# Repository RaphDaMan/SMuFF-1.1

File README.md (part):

# Welcome to the SMuFF project

Here's the official firmware package for the **S**mart **Mu**lti **F**ilament **F**eeder, as published on [Printables](https://www.printables.com/de/model/194737-smuff-v6-smart-multi-filament-feeder-with-bondtech) and [Thingiverse](https://www.thingiverse.com/thing:3431438). Read the full story on how it came to life on my official [SMuFF homepage](https://sites.google.com/view/the-smuff/).

If you like this project and find it useful, you may consider [donating](https://sites.google.com/view/the-smuff/downloads/assembly-manual#h.m5ewgcp0jfk6).

To use this firmware, you have to [compile it](https://sites.google.com/view/the-smuff/how-to/tutorials/compile-the-firmware?authuser=0) and flash it to one of these (already supported) controller boards:

| Board |  |
|------------|-----|
| Bigtreetech [SKR mini E3 V3.0](https://www.biqu.equipment/products/bigtreetech-skr-mini-e3-v2-0-32-bit-control-board-for-ender-3) |**recommended** |
| Bigtreetech [SKR mini E3-DIP V1.1](https://www.biqu.equipment/products/bigtreetech-skr-e3-dip-v1-0-motherboard-for-ender-3)||
| Bigtreetech [SKR mini E3 V2.0](https://www.biqu.equipment/products/bigtreetech-skr-mini-e3-v2-0-32-bit-control-board-integrated-tmc2209-uart-for-ender-4) ||
| Bigtreetech [SKR mini V1.1](https://www.biqu.equipment/collections/control-board/products/bigtreetech-skr-mini-v1-1-motherboard-32-bit-arm-equipped-with-tmc2208-v2-1-tmc2130-spi-driver-stepstick-for-3d-printer-desktop?variant=20361870377058)||

The Bigtreetech SKR mini series boards are very small and yet powerful because of the 32-Bit STM Microcontroller Unit.

Of course, this firmware can also be configured to run on any other controller board, as long as it meets the specifications. Although you might be able to utilize older 8 bit boards, I don't recommended it - you'll most probably run out of memory (Flash/RAM) very soon. I recommend using a 32 bit controller board instead.
Make sure your board of choice has at least **256K** of Flash memory, **48K** of (S)RAM and all other components needed, which are at least:

+ two stepper motor drivers (sockets)
+ two endstop connectors
+ one servo connector (or two spare I/O pins for Software-I2C)
+ an onboard SD-Card
+ one spare serial port (USB or TTL)
+ a 128 x 64 pixel display connector
+ a rotary encoder connector

Simply create a new build environment in your **platformio.ini** and adopt the settings according to your controllers hardware in your custom **pins.h** file.

The configuration files **\*.json** and **debug.txt** have to be copied into the root folder of your SD-Card for the controller board. Hence, changing runtime parameters doesn't require recompiling the firmware. Just edit the settings from within the built-in menus or the [WebInterface](https://github.com/technik-gegg/SMuFF-WI), save them and reboot.

I've added the option to run GCode scripts for automated testing of your hardware.
In the **test** folder you'll find some sample scripts. Copy the folder over to your SD-Card and pick a script from within the menu to start the test run. Once started, the test will run infinitelly until you stop it.
Each test result will be displayed on the LCD and also sent to the log serial port (which is the USB port, if not defined otherwise).

For more information about building the SMuFF and some more detailed stuff, head over to my official [SMuFF homepage](https://sites.google.com/view/the-smuff/) or to my [Discord server](https://discord.com/invite/BzZ3rBf).

---

## Credit where credit is due

A special thanks to the folks who have shared the following libraries/knowledge, on which the SMuFF firmware builds upon:

+ [Adafruit](https://github.com/technik-gegg/Adafruit-PWM-Servo-Driver-Library.git) for the PWM Servo library
+ [Benoît Blanchon](https://github.com/bblanchon/ArduinoJson.git) for the Arduino JSON library
+ [Bill Greinman](https://github.com/greiman/SdFat) for the SD-Card library
+ [Oliver Kraus](https://github.com/olikraus/U8G2_Arduino.git) for the U8G2 display library
+ [teemuatlut](https://github.com/teemuatlut/TMCStepper) for the TMC-Stepper library
+ [the creators of the](https://github.com/technik-gegg/SoftWireSTM32/) SoftWireSTM32 library
+ [Tom Schimansky](https://github.com/TomSchimansky/CustomTkinter) for the Custom Tkinter Python package
+ [Akash Bora](https://github.com/Akascape) for the CTkMessagebox and CTkToolTip packages
+ [Scott Campbell](https://www.circuitbasics.com/arduino-thermistor-temperature-sensor-tutorial/) for sharing his knowledge about Thermistor handling

---

## Recent changes

**3.30** - Filament-Dryer integration

+ added fully functional Filament-Dryer (controller) by utilizing the Bed-Heater and Thermistor on the SKR E3 V3.0 board. Read all the details about this new feature [here](https://sites.google.com/view/the-smuff/how-to/build/the-filament-dryer). In order to use it, you have to compile the firmware with the *USE_DRYER* option and copy the new **dryer.mnu**, the updated **main{0-4}.mnu** files over to the *menus* folder and the **DRYER.json** file to the root folder of the SMuFFs SD-Card. Also copy the *help* folder to the SD-Card, since some GCodes were added/updated.
+ added GCode **M141** for controlling the new Filament-Dryer feature.
+ updated GCode **M106** in order to enable controlling fans 1 & 2 for the Filament-Dryer (will work only on SKR E3 V3.0).

**3.29** - Integrated Heater functions / SMuFF-Backbone

+ added code to control the (Bed-) heater on the SKR E3 V3.0.
+ added some code changes needed for the [SMuFF-Backbone board](https://sites.google.com/view/the-smuff/how-to/build/the-smuff-backbone).

**3.28** - minor changes

+ added option for 4th DC motor driver board (Waveshare/FeatherWing - for future use).
+ added option for up to two AHT-10 Temperature/Humidity sensor boards (for future use).
+ added GCode **M105** for reading out Temp./Humidity sensors.
+ refactored some of the code, i.e. moved code from SMuFF.cpp to own modules.

**3.27** - minor bug fixes

+ fixed bug on **FeatherWing DC-Motor Board** causing not all motors were able to spin because of the wrong pin assignment.
+ corrected help files for **M3/M4** GCodes (parameter **S** denotes the **Tool** but not neccessarily the **Motor** number).
+ fixed bug on **SKR E3-DIP V1.1** not beinig able to set relay pin to **Y-STOP** due to conditional compiling constraints.
+ corrected some flaws in *testrun()* not correctly reporting "feeding errors" as they occur.

**3.26** - minor change

+ moved scanning for I2C devices after display has been initialized, so it becomes obvious when the I2C scan is hanging, which happens if no I2C devices are attached to the bus.

**3.25** - minor fixes/changes

+ restricted scanning of the I2C bus to valid slave addresses (0-7 and 120-127 are reserved addresses). Although this didn't cause any error yet, it could have caused some unwanted effects in the future.
+ added a new option to route debug messages to other than the default Serial 2 (a.k.a. TFT-Header): Create a file in the root folder of the SD-Card named:
  + **dbg2usb.txt** for Serial 0 (a.k.a. USB)
  + **dbg2exp.txt** for Serial 1
  + **dbg2oth.txt** for Serial 3

   **Keep in mind:** These files need no content. Not every port (except USB) is available on every board, it depends on board and configuration. To reset sending debug messages to default Serial 2, delete or rename the file.
+ added the **Adafruit Stepper + DC Motor FeatherWing** board as a 2nd option for the Spool-Rewinder controller. To use it, you have to define **USE_SPOOLMOTOR_FEATHERWING** in addition to **USE_SPOOLMOTOR** in the *config_defaults* and/or tick the according option in the *Firmware Build Configurator*.

**3.24** - added new "Firmware-Build Configurator"

+ made the build configuration easier by adding a custom dialog (Python/Ctk). Now, the *PROJECT TASKS* treeview only contains the basic build environments for each supported controller. Everything else can now be configured right after clicking on the **Build** task using this dialog:

This is by far more convenient than parsing through the *platformio.ini* or trying to find the build environment you want.
Tooltips will show up when hovering over the checkboxes, which briefly explain why you would use this option.
After the build you'll find a **readme-build.txt** file in the output folder, listing the options that have been set for this particular build.
To define a set of **personalized default settings** depending on the controller used, one can list them under the *config_defaults* section in *platformio.ini*.
*Please be aware that for using this feature, PlatformIO needs to install some Python packages once. This happens automatically at your very first build.*
+ updated SdFat library reference to 2.2.0
+ added the option to use the "old" clock settings (those recommended by STM) for the SKR E3 V3.0 board instead of the new ones introduced in version 3.23.
+ added a couple more debug messages while the firmware is being initialized.

**3.23** - bugfix, Motorized Spool Rewinder option added

+ fixed the bug that caused some (newer) SKR E3 V3.0 boards not being recognized (enumerated) when connected via USB.
+ added **_SPM** build environments, which allow utilizing the [Motorized Spool Rewinder](https://sites.google.com/view/the-smuff/how-to/build/the-spool-rewinder). To use this option, you have to copy the *help* and *menus* folders to your SMuFFs SD-Card. Also, please notice the added content in **MATERIALS.json**.
+ added GCodes **M3**, **M4** and **M5** to allow controlling the spool motors of the *Motorized Spool Rewinder*.

**3.22** - reorganized Build Environments

+ reorganized Build Environments as announced in 3.21.
.
+ added include of <stdint.h> to SMuFF.h, since latest builds seem to fail.

**3.21** - some changes based on the previous release

+ reworked the Build Environments in **platformio.ini**
 Since the **SKR E3 V3.0** has become the most dominant contoller board and the others are getting more and more outdated, I've decided to get rid of some of the Build Environments for "older boards" and add all the possible permutations for the E3 V3.0 instead. The suffixes are meant to be self-explanatory but as a hint: **NPX** means NeoPixels (on tools), **MS** means Multiservo and **DDE** means Direct Drive Extruder.
 Here's what the *PROJECT TASKS* treeview in VSCode now looks like:
 
 Simply open the Build Enviroment that matches your setup and click on "Build".
 Outdated Build Environments are still contained in the ini-file but need to be un-commented in order to make them show up in the *PROJECT TASKS* treeview.
+ the (FYSECT / BTT / MKS) **MiniPanel 12864 V2.1** display has become the default option now. It's the cheapest and easiest to source display, so I declared it the "standard".
+ while playing around with the new behaviour of **USE_NUM_PIXELS** introduced in the previous release, I figured, it's far easier to have the number of LEDs configurable at runtime and thus, I've moved it to the SMuFF configuration file. Hence, this definition is now gone from the platformio.ini!
When you update to this version, please keep in mind to also copy the new **display.mnu** and **m205.txt** to your SMuFF's SD-Card, into the folders *menu* and *help* accordingly.
+ I also found an unpleasant but logical behavior in the *Marquee* animation when more than 7 LEDs are in use: It skips LEDs because on the beatsin() calculation and BPM settings, so I fixed that.
+ while I was at it, I also added two new Idle-Animations: Rainbow and Cylone. Thus, you need to copy the **anim-type.opt** to the *options* folder as well. Then pick the one that you fancy the most from the *Display menu*.

**3.20** - small feature change

+ corrected the behaviour of the **USE_NUM_PIXELS** definition in *platformio.ini*. This defines how many **NeoPixel LEDs** one plans to use for one tool (which usually is: "1 LED per tool").
This feature comes in handy when you're using a NeoPixel strip with a higher density. The "standard" NeoPixel strips come with a density of 60 LEDs/meter but they're also available in 30, 72, 96, 144, 240 or even 332 LEDs/m.
It turned out, that on strips with **144 LEDs/m** the LED spacing is around 7mm (i.e. 1000/144 = 6.94), which corresponds to 3 LEDs for 21mm! Coincidentally, this is also the exact width of one Filament-Guide. Hence, using a 144 LED/m strip saves you from the tedious job of cutting a strip and re-soldering the LEDs in order to get them into the right position. Simply use a longer strip (3 LEDs * number_of_tools) and set **USE_NUM_PIXELS** to 3 before compiling the firmware.

**3.19** - bug fix

+ fixed bug in Selector homing. When homed, SMuFF wasn't able to select tools because the Selector endstop was still triggering.

**3.18** - minor bug fix

+ fixed bug in displaying menu items

**3.17** - minor bug fixes / optimizations

+ fixed bug in platformio.ini for SKR Mini environment.
+ fixed bug in *NeoPixels on Tools*, if more than 5 tools are being used. Init of the NeoPixels happened before the Config was read and hence the count of tools/NeoPixels was incorrect.
+ optimized code for the steppers (*ZStepperLib*) yet again. The *isrStepperTimerHandler()* method now has an overall runtime of about **15uS** on a **STM32F1** MCU running at 72MHz.
+ changed some methods in timers.h/timers.cpp in order to shave off some microseconds in processing time.
+ fixed bug in synchronous movement of the steppers. Feeder stepper wasn't moving at the same pace as the DDE Feeder.
+ changed the USB signature to **STMicroelectronics SMuFF 3.x**. This way it's easier to distinguish which controller is for the SMuFF on the Raspberry Pi.
+ added meaningfull description headers to all methods in *ZStepperLib*, so it can be reused in other projects.
+ moved hardware Debug-Pin for E3-DIP controller from **Y-STOP** to **SWCLK** for a cleaner wave form. Since this is for my debugging only, you don't have to care much about this change.
+ removed TMC library and build flags from **E3-DIP** and **SKR MINI**, since those boards have no native TMC support (i.e. not being controlled through serial or SPI) and hence TMC drivers are running in "Standalone" a.k.a. "A4988" mode.
+ modified the **Acceleration Distance** behaviour. If this value is set to **0**, SMuFF will use 20% of the total distance for accel/decel, which results in a somewhat smoother acceleration/deceleration.
+ fixed bug stepper movement not stopping on endstop trigger. For some (still undiscovered) reason, the endstop ISR doesn't fire while steppers are moving.
+ changed/removed a couple of debug messages to make them a bit more meaningful.

**3.16** - bug fixes / enhancements / cleanup

+ **changed the stepper motors timer prescaler from 24Mhz to 2MHz** (internally 4MHz). This means, you **must** adjust your stepper ticks, otherwise steppers are going to turn terribly slow! Had to do this in order to gain more granular control over the stepper motors at lower speeds.
*Rule of thumb: Divide your current speed settings (Max. speed, Accel. speed, Purge speed, etc.) roughly by 10.*
The stepper timer in fact is running on double the frequency (4MHz) in order to achieve a longer pulse on the stepper driver, because now every 1st tick is used to set the STEP signal, every 2nd to reset the STEP signal. This makes the *Step-Delay* setting unnecessary and you should set it to 0. Though I left this setting in the config, just in case one needs it.
+ changed behaviour of "Unload retraction". If a value is set, it will only be executed if filament is fully loaded (down to nozzle). Keep in mind that this feature is used to shorten the filament remains when using the Cutter and yet only works on a Bowden setup.
+ changed data-type in *purgeFilament()* from uint16_t to double for more accurate purging.
+ changed the method of debug outputs in endstop interrupt functions, since sending data to serial ports from within ISR routines is always a bit critical and may block or crash the controller.
+ added **DEV4** debug flag for a more granular output control of debug messages (i.e. printing incoming GCodes, memory stats, ...).
+ updated GCode **M100** to determine free system memory (RAM). Before, this GCode only returned "ok".
+ added printing out memory stats every minute if *DEV4* debug flag is set.
+ removed the "*Mirroring the display on a VT-100 terminal*" feature introduced in V2.24 completely. Although it was nice to have back then, the software options around the SMuFF have evolved. Hence this feature is obsolete now and was only messing up the source code.
+ removed the (meanwhile) obsolete conditional code for FastLED library. My modified Adafruit NeoPixel library is covering all that's needed.
+ overhauled the code for handling the NeoPixels on tools. NeoPixels will not update as long as one of the stepper motors is spinning (Feeder / Selector), which makes the steppers run smoother.
+ added parameter **P** to GCode **M700** (load filament) in order to purge material (after it's being loaded). If no *value* (e.g. *M700 P*) is given, it'll purge the configured purge amount, otherwise the length of filament given in *value* (e.g. *M700 P12.34*).

  **[ Bug fixes ]**

+ fixed the bug that puts a "loading" dialog on the display while in *Testrun mode* (kudos to **palkovnik807**).
+ fixed the bug where retries were not being decremented while unloading filament (a.k.a "infinite loop" if unloading went wrong).
+ fixed a potential buffer overflow in *drawPurgingMessage()* and *printPeriodicalState()* functions.
+ fixed a bug that may have caused the MS1/MS2/MS3 pins being set up wrong on the **E3-DIP V1.1** (only), because the according pins on the MCU were in an undefined state. Now those pins are being set to LOW (0V) at startup.

**3.15** - minor changes / bug fixes

+ added option **NEVER_DISABLE_SERVOS** in *platformio.ini* section *'other'* which will inhibit disabling servos after they had been moved. The default behaviour is that the SMuFF will disable the PWM signal on **Wiper** and **Cutter** servos after wiping/cutting, because some servos run less jittery when disabled.
However, it turned out that disabling the PWM signal on some servos causes those servos eventually start moving out of the blue. Allowing the PWM signal to stay active helped fixing this issue.
If you discover random movements on your Wiper/Cutter servo, activate this new option before compiling the firmware.
*This option however doesn't influence the behaviour on the Multiservo board(s) - which still are the better option for driving servos.*
+ fixed the bug that sometimes caused the filament not being fully retracted (i.e. Feeder endstop not triggered). Happens only if the configured "Bowden length" value doesn't match the real distance or the filament "slipped" during retraction. In such case the Feeder was supposed to retry until the endstop has triggered but didn't due to wrong condition checking. Thanks to **palkovnik807** on Discord for pointing it out.
+ fixed the bug that caused the **DDE Feeder** not doing a purge under certain conditions because the stepper wasn't enabled. Thanks to **Thyom** on Discord for finding it.
+ added printout of DDE Feeder endstop state for GCode **M119**, in case SMuFF is configured for DDE.

**3.14** - minor changes / bug fix

+ added option **USE_NUM_PIXELS** in *platformio.ini*. Usually, the number of Neopixels matches the number of tools but in some special case you may have more Neopixels on your strip then tools. In order to make the animations using all pixels, enable this definition and set its value to the according number.
+ fixed bug where Lid servo didn't close before unloading when Cutter has been configured as sitting "on top".

**3.13** - Changes for Duet3D and Serial display / some bugfixes

+ fixed bug in TMC driver **Stealth-Mode setting** via SMuFF-WI. Value was accidentally inverted.
+ fixed bug that caused a compilation failure when using the *SKR_E3_30_RET6___DDE* build environment.
+ added [SMuFF-Backbone](https://sites.google.com/view/the-smuff/work-in-progress?authuser=0#h.m19pbkoy3v6p) schematic and PCB design.
+ added **DuetSerial** (port) setting to **SMUFF.json** and menus. You **must** now define the serial port where the Duet3D/RRF is connected to (set to Ser.1 by default). This serial port will only be taken into account if the SMuFF is configured for Duet3D/RRF. For this option you need to copy the modified **options.mnu** and **duet3d.opt** files into the according folders on your SMuFFs SD-Card.
+ added **DspSerial** (port) setting to **SMUFF.json**. The Display serial port can only be configured either through the **-D DISPLAY_SERIAL_PORT** definition in *platformio.ini* or manually in SMUFF.json but not from the menus (because there will be no menus in this mode). See notes on **USE_SERIAL_DISPLAY** for version **3.00** down below.
+ updated **M42** & **M280** & **M205** help files (for Multiservo use).
+ added Dialogs and Sound support on SMuFF-WI when *USE_DISPLAY_SERIAL* is enabled.
+ added **SWAP_SELECTOR_ENDSTOP** build option for those who experience the X-STOP (used for Selector) is not being triggered on a **SKR E3 V3.0**. With this option enabled, the firmware expects the Selector endstop to be connected to *Y-STOP* rather than *X-STOP*.
+ added *JAM* flag in periodical status messages; This is being used in my OctoPrint/Klipper plugins to indicate whether or not the tool change has failed for some reason.
+ added option to switch the *Debugger Serial Port* from within **debug.txt** on startup, without the need for recompiling the firmware. To use this option simply add a **;x** after the value, whereas *x* determines a port number between **0** and **3**. Port **0** always indicates the **USB** serial port, whereas ports **1..3** depend on the controller board you're using (*port 2 is the default value and is assigned to the **TFT** header on most boards*).
*Keep in mind:* This setting will vanish once you set the debug flags via GCode **M111** and store them using **M500**.
+ added option to switch the *Debugger Serial Port* on the fly via **M205** GCode. To use it, simply apply parameters **P"ChangeDbg" Sx**, whereas *x* is the number of the new serial port in the range of **0..3** (see description above).
*Keep in mind:* This setting is temporary and will be reset at the next boot.
+ added option to filter in help files. After the **?** append the phrase to filter for. For example: **M205?dist** will only show the header and all lines containing the string *"dist"*.

**3.12** - Changes for the MULTISERVO option

+ reworked **MULTISERVO** option. For one it's now named *USE_MULTISERVO* for more consistency throughout the other options. For the other, it's now being used to configure all servos to control them via an external board (Adafruit Multiservo/FeatherWing/ [SMuFF-Backbone](https://sites.google.com/view/the-smuff/work-in-progress?authuser=0#h.m19pbkoy3v6p) board). This external board is always being controlled by using software I2C. The pins used for SW-I2C vary throughout the different controller boards.
+ the **USE_MULTISERVO** flag will become more importance in the future, hence I moved that option to the *[other]* section of *platformio.ini*.
+ modified the external **SoftWireSTM32 library** which had a bug that caused that the library wasn't able to scan for devices on the I2C bus properly.
+ moved relay control pin on **SKR mini E3-DIP V1.1** from **MS3** pin of the Z-Axis driver socket (in DDE mode) to the **TH0** pin if the **USE_MULTISERVO** flag is set. This is because this signal is being used as the data pin (SDA) for the software I2C controlling the Adafruit Multiservo board.
+ added **USE_MULTISERVO_RELAY** flag to the compile options in order to control the relay via output #5 on the Multiservo board instead of *MS3*, *TH0* or *PROBE* pins. This will be the future method of controlling the relay switch. **Please notice:** This method requires a pull-up resistor of 4.7K - 10K, either on +5V or +3.3V to make the signal switch as intended. The reason being is that the outputs on the Multiservo board are configured as open-drain.
+ corrected build environment for **SKR mini V1.1** (FastLED library was still referenced instead of the Adafruit Neopixel library).
+ fixed the bug that caused the **SKR mini V1.1** to hang at startup (wrong *debugSerial* port has been initialized).
+ added a couple more meaningful error messages to the GCode interpreter.
+ changed **SERVOMAP.json** config file to reflect the new MUTISERVO options. Please copy this file over to your SMuFF's SD-Card.
+ changed **ServoMinPwm** and **ServoMaxPwm** settings in SMUFF.json. These settings work better with the Multiservo boards. Copy the modified file over to your SMuFF's SD-Card and don't forget to reconfigure your servo angle settings.
+ added the two user controlled servo ports (USER1/USER2) to **M280** GCode and **M42** GCode when using the MULTISERVO option. Send M280 P1000 / P1001 if those ports are supposed to drive custom servos, or M42 P1000 / P1001 if those ports are configured to be used as output pins (i.e. to be switched on/off).
+ added **M260** GCode to allow scanning for I2C devices at runtime using the GCode interface.
+ updated some of the KiCad files to KiCad version 6.x

**3.11** - Some minor changes

+ added flashing of the "Periodical State sending" glyph on the display when it's enabled. Flashing happens at half the frequency of states being sent.
+ added current relay state (**E** / **I**) to "Periodical States".
+ changed output of **M122W** and **M503W**. *M122W9* and *M503W0* are now sending all state/configuration data at once, which makes SMuFF-WI connect faster.

**3.10** - Some minor changes / bug fixes

+ **removed SKR E3 V1.2** from the list of supported devices because this board isn't optimal for the SMuFF V6. Consider moving to E3 V2.0 or better E3 V3.0.
+ changed some default settings in *SMUFF.json* which fits better for V6 default configuration.
+ switched from FastLED to AdafruitNeoPixel library throughout for all boards.
+ fixed bug where DDE extruder wasn't reading out the endstop while retracting.
+ fixed bug with NeoPixel refresh.
+ added dedicated timer for NeoPixel refresh because the existing solution interfered with servos and steppers.
+ (re-) added timer for servos because the existing solution interfered with the stepper timer.
+ changed timer priorities and intervals to get rid of servo jitter.
+ changed priority on timers, so the stepper timer (and thus the stepper movement) is a bit more agile now.
+ added GCode command **M155** for fast switching of *sending periodical status messages*.
+ GCode **M205 help file** updated.
+ cleaned up *platformio.ini* by extending environments in *__DDE.
+ added GCode command **M562** to reset a *Feeder Jam* remotly.
+ added more status/error responses in order to make the Klipper module run smooth
+ added feeder states (SPL in periodical states) for all variants. This value is now (lower nibble: Splitter, upper nibble: non-Splitter):
  + 0x00 means *not loaded*
  + 0x01 means *loaded to Splitter*
  + 0x02 means *loaded to Nozzle*
  + 0x10 means *loaded to Selector*
  + 0x20 means *loaded to Nozzle*
  + 0x40 means *loaded to DDE*
+ added "JAMMED" state on display when feeder is being jammed

**3.00** - Moving from Maple to Arduino Core STM32 framework  

+ ported firmware from **Maple** to new **Arduino Core STM32** (stm32duino) framework in order to make boards with different MCUs available. This version is still compatible with the predecessor SKR controller boards, such as the SKR Mini/E3-DIP/V2.0.
+ added **debug.txt** to define the amount of debug messages being spit out without re-compiling the firmware. Also added the option of changing the debug level through GCode, which is **M111**. See *M111?* for details.
+ compiling the firmware without the **-D DEBUG** option will now reduce the memory footprint drastically. Although, removing debug messages completely will make your first setup much harder, so handle with care.
+ updated help files in *help* folder.
+ reduced the number of build environments in *platformio.ini*. Please note that **USE_DUET3D** has become obsolete and is now a runtime option. However, the **USE_DDE** flag still is the same and hence it's got its own build environment (*\*___DDE*).
+ added build options summary when compiling. This makes checking the build options you've set a breeze:

+ removed Servo-Timer. Servos are now served through the *General Purpose Timer*, which makes the servo timing more percise and thus the servos less jittery.
+ added flag **MIMIC_LIBMAPLE_USB_ID** in order to keep the USB ID compatible for use with my [OctoPrint plugin](https://github.com/technik-gegg/OctoPrint-Smuff). This setting is default for the "old" SKR E3 controller boards but not for newer boards.
+ added flag **SWAP_SERVOS** which will assign the Lid and the Cutter servos to the BL-Touch header for SKR E3 V1.2 / V2.0 / V3.0 (it swaps Wiper and Cutter servo signal pins).
+ added new build environment for **SKR E3 V3.0** controller board. This board has been fully tested and is ready to use.
+ added new build environment for **SKR E3 RRF** controller board. **Not tested yet!**
+ added **SyncSteppers** flag in SMUFF.json, which, if turned on, synchronizes movement of two or more steppers, so that they start and finish at the same time. Set by default.
+ eliminated code for *ZPortExpander* completely.
+ restructured **Options** menu on the display. Copy the new *options.mnu* file to the SMuFFs SD-Card (folder menus).
+ added **USE_SERIAL_DISPLAY** option for future use. ***Please be aware:** By setting this flag, no display code will be compiled into the firmware and hence the only way to control it is by using the WebInterface.*
+ added **USE_FAST_SW_SPI** build option for Creality  displays (or compatibles such as the BTT TFT). This allows you to simply connect the display through EXP1/EXP3 with the applied 10 pin cable, and still get a decent speed and responsiveness on the display.
+ added a couple of new STL files for Inlet-Guides and new SKR housing. Inlet-Guides are now available for 5 and 7 materials (thanks to maker **Defenc**). For a different amount of materials on the Inlet-Guides, please download the according [STEP file from Thangs](https://thangs.com/mythangs/file/55305).
+ fixed bug which caused the SMuFF to hang after showing the main menu.
+ refactored some code from **SMuFFtools.cpp** into *DisplayTools.cpp*, *SoundTools.cpp* *ServoTools.cpp* and *TerminalTools.cpp* for better maintainability.

---

**2.44** - Addition for alternative RRF boards

+ added inverting option for the *Busy* signal that goes to a endstop of a RepRap Firmware board (other than the Duet3D). This was needed since some of the alternatives might not be able to trigger upon the original signal. To use this option, you'll also need to copy the updated **options.mnu** file to the *menus* folder of your SMuFFs SD-Card.
Basic instructions for setting up a RRF (Duet3D) board can be found [here](https://sites.google.com/view/the-smuff/how-to/tutorials/configure-the-duet3d?authuser=0).
+ removed old code that might have disturbed Duet3D signals.
+ fixed a typo in the folder name which caused the E3 V1.2 version not being able to build correctly.
+ reorganized *Build Environments* in platformio.ini. This change allows you to pick some of the build options quickly. In the *Project Tasks* you'll now find different environments named after the controller board (i.e. **SKR_E3_12** for the SKR E3 Version 1.2) and three with the same name plus an extension named either **DDE**, **DUET** or **DDE+DUET**. The one without an extension is the "basic" version (no DDE, no Duet3D). **DDE** builds the firmware for the DDE option, **DUET** for the Duet3D (a.k.a. RRF) and **DDE+DUET** for a combination of both of the previously mentioned options. Thus, you don't have to mess with these settings in the [options] / [extruder] section anymore (the latter section has become obsolete now).
Keep in mind that you still have to set the correct **display** option before you build the firmware, in case you're using something else than the DIY display.
+ added **M118** GCode to enable you to send text (GCode) from the SMuFF/WI console to a specific serial port. Parameters are the same as for Duet3D/RRF fimrware, whereas **P**x defines the serial port, and **S**"..." defines the message to send. Please update you *help* folder with the latest files.

**2.43** - added new STLs

+ added new STL files for the small servo carrier. Please read [the instructions posted here](https://sites.google.com/view/the-smuff/work-in-progress?authuser=0#h.ssx9ayceh6f4).
+ updated version number to make the version check in WebInterface happy again.

**2.42** - some minor bug fixes/changes

+ made contrast setting a live function (contrast of the display will change as you rotate the knob, which makes it easier to set up).
+ corrected contrast setting after reading configuration on startup.
+ changed backlight color order on *FYSETC Minipanel* from GRB to RGB.
+ added SKR E3 RRF board to the collection. **This is experimental only and will not compile due to the lack of support for STM32F4 in some libraries. Do not use!**

**2.41** - some fine tuning on recent changes

+ added **DebugFreq** setting to **SMUFF.json** which allows to set the frequency (in Hz) applied to the hardware debug pin for testing purposes. This value can be changed during runtime via M205 GCode as well.
+ defined Duet3D signal pins (*DUET_SIG_FED_PIN* and *DUET_SIG_SEL_PIN*) to be on thermistor pins (THB and TH0). Because of the R/C filter on those pins signals are limited to a max. switching frequency of **100Hz**, which is sufficient for this purpose.
+ removed redundancy in display includes throughout all the Pins.h files. These are now located once in *Display/Display.h*.
+ corrected some pin defintions in all Pins.h files.
+ revived the SKR Mini V1.1 board (because it's still available and in use).

**2.40** - code reorganization and bug fixing

+ removed old boards, such as ESP32, SKR Mini, FYSETC AIO II, mainly because they're discontinued and just mess up the project.
*Because of this change the version number is now 2.4*
+ removed code for ESP32 entirely. As long as the ESP32 has such a deficit on I/O pins, it's not feasible as a SMuFF controller.
+ split up **Pins.h** to disentangle the confusing code for display pin definitions. Now each display type has it's own *DSP_xxx.h* header file and the initialization takes place in the according *Display/xxx.h* file instead of *SMuFF.cpp* and *SMuFF.h*.
+ reorganized code in order to reduce memory footprint and allow compiling for NeoPixels unconditionally. Due to usage of the PortExpander (PCF857X), which only purpose was to extend the amount of I/O ports on the ESP32, the memory footprint exploded. It's corrected now and the memory (RAM) footprint is slightly around 35% instead of 86%!
+ corrected pinout for standard RepRap display and FYSETC 12864 Minipanel on E3 V2.0 board.
+ improved drawing speed on the DIY OLED display for E3 V2.0 board.

**2.34 - 2.39** - skipped versions

**2.33** - bug fixing for DDE option

+ fixed a bug that caused stalling on the DDE stepper motor while purging because of wrong settings.
+ added more frequent status information for the WebInterface while swapping tools.

**2.32** - added Cutter position for DDE option

+ **moved main repository on Github to SMuFF-2.0 branch. No need to download from the SMuFF-2.0-(Experimental) anymore.**
+ added **CutterTop** option in SMUFF.json which was needed for the latest Orbiter-Extruder mod. For the Orbiter-Extruder you need to set this option to *false* because the Cutter sits below the DDE.

**2.31** - added Cutter handling for DDE option

+ added purging of filament when DDE is being used in conjunction with the Cutter in order to release the 2nd endstop. To use this, set the **PurgeDDE** flag in SMUFF.json accordingly.
+ fixed bug in feedToEndstop which caused an abort if the *InsLen* parameter was set too low.
+ added all **STL files** for V6 to this repository
+ added **Device** parameter in SMUFF.json. This string can be 15 charaters long and sets a distinct name for the current SMuFF device (i.e. the printer it is attached to). The name of the device will be show up in the WebInterface and also in GCode **M503**. This name can only be set/changed through the WebInterface or directly in the config file but not in the menu.

**2.30** - DDE option added

+ added **USE_DDE** flag in platformio.ini. Set this flag if you intend using the SMuFF on a Direct Drive Extruder. Further instructions you'll find on the [SMuFFs website](https://sites.google.com/view/the-smuff/how-to/tutorials/set-up-a-dde).
+ added new menu items in **options** menu for DDE. *Please notice:* The Use DDE flag can't be switched during runtime, it's only shown to indicate whether ot not this firmware was compiled for DDE.

**2.29** - Some critical changes, Splitter option added

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
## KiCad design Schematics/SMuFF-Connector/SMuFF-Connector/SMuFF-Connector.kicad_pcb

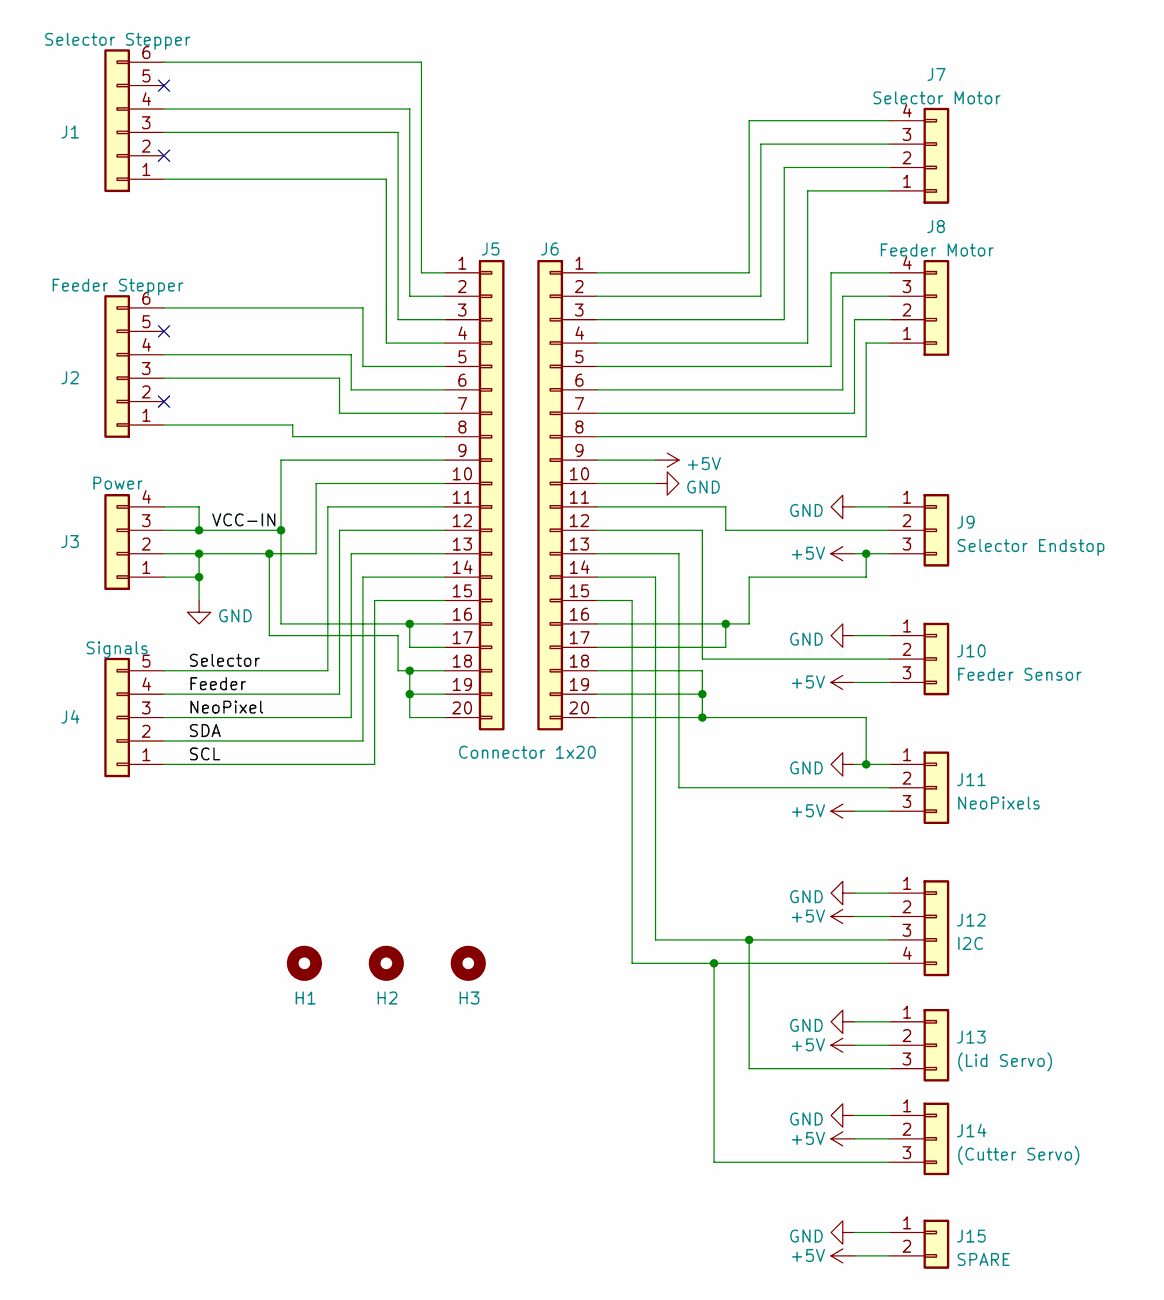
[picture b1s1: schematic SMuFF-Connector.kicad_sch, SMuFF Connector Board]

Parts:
H1, H2, H3: MountingHole; MountingHole_3mm
J1: Selector Stepper; JST_PH_B6B-PH-K_1x06_P2.00mm_Vertical
J2: Feeder Stepper; JST_PH_B6B-PH-K_1x06_P2.00mm_Vertical
J3: Power; JST_XH_B4B-XH-A_1x04_P2.50mm_Vertical
J4: Signals; JST_XH_B5B-XH-A_1x05_P2.50mm_Vertical
J5: Connector 1x20; PinHeader_1x20_P1.27mm_Vertical
J6: Conn_01x16; PinHeader_1x20_P1.27mm_Vertical
J7: Selector Motor; JST_XH_B4B-XH-A_1x04_P2.50mm_Vertical
J8: Feeder Motor; JST_XH_B4B-XH-A_1x04_P2.50mm_Vertical
J9: Selector Endstop; JST_XH_B3B-XH-A_1x03_P2.50mm_Vertical
J10: Feeder Sensor; JST_XH_B3B-XH-A_1x03_P2.50mm_Vertical
J11: NeoPixels; JST_XH_B3B-XH-A_1x03_P2.50mm_Vertical
J12: I2C; JST_XH_B4B-XH-A_1x04_P2.50mm_Vertical
J13: (Lid Servo); PinHeader_1x03_P2.54mm_Vertical
J14: (Cutter Servo); PinHeader_1x03_P2.54mm_Vertical
J15: SPARE; JST_XH_B2B-XH-A_1x02_P2.50mm_Vertical

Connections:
+5V: J6.9, J6.16, J6.17, J9.3, J10.3, J11.3, J12.2, J13.2, J14.2, J15.2
/Feeder: J4.4, J5.12
/NeoPixel: J4.3, J5.13
/SCL: J4.1, J5.15
/SDA: J4.2, J5.14
/Selector: J4.5, J5.11
/VCC-IN: J3.3, J3.4, J5.9, J5.16, J5.17
GND: J3.1, J3.2, J5.10, J5.18, J5.19, J5.20, J6.10, J6.18, J6.19, J6.20, J9.1, J10.1, J11.1, J12.1, J13.1, J14.1, J15.1
unnamed: J1.1, J5.4
unnamed: J1.3, J5.3
unnamed: J1.4, J5.2
unnamed: J1.6, J5.1
unnamed: J2.1, J5.8
unnamed: J2.3, J5.7
unnamed: J2.4, J5.6
unnamed: J2.6, J5.5
unnamed: J6.1, J7.4
unnamed: J6.2, J7.3
unnamed: J6.3, J7.2
unnamed: J6.4, J7.1
unnamed: J6.5, J8.4
unnamed: J6.6, J8.3
unnamed: J6.7, J8.2
unnamed: J6.8, J8.1
unnamed: J6.11, J9.2
unnamed: J6.13, J11.2
unnamed: J6.12, J10.2
unnamed: J6.14, J12.3, J13.3
unnamed: J6.15, J12.4, J14.3

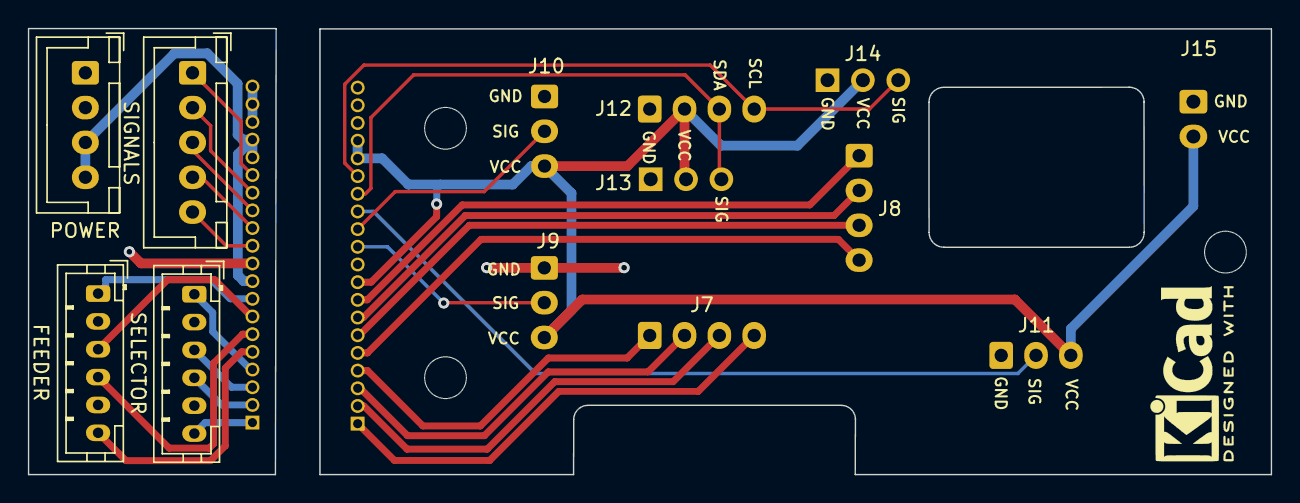
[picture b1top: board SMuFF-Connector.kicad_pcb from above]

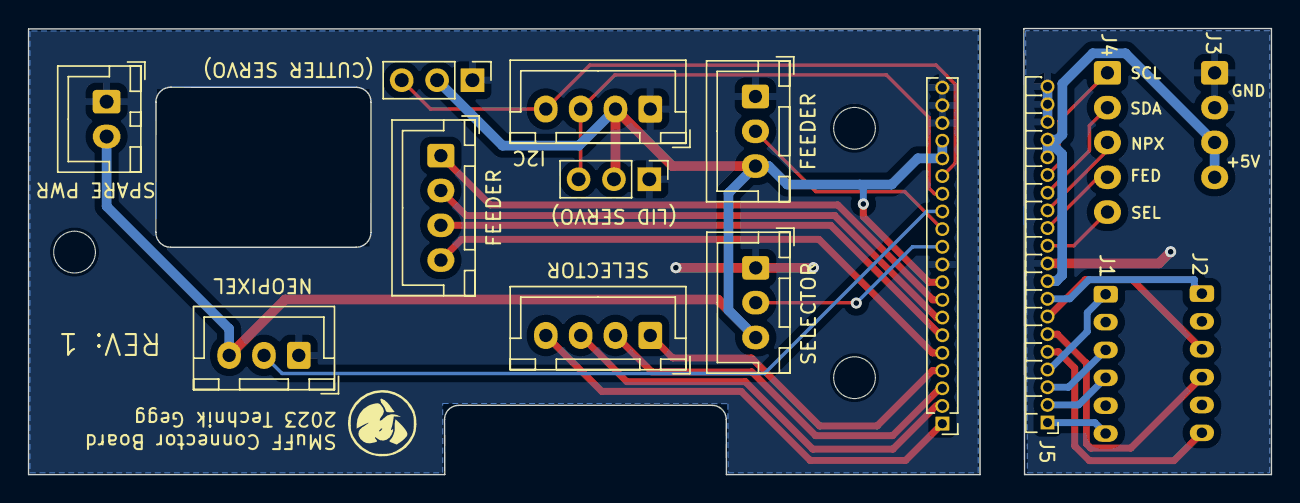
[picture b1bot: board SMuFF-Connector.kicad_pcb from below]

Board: 2 copper layers, 89.2 x 32.0 mm, 18 parts (11 on the bottom side), 29 nets.

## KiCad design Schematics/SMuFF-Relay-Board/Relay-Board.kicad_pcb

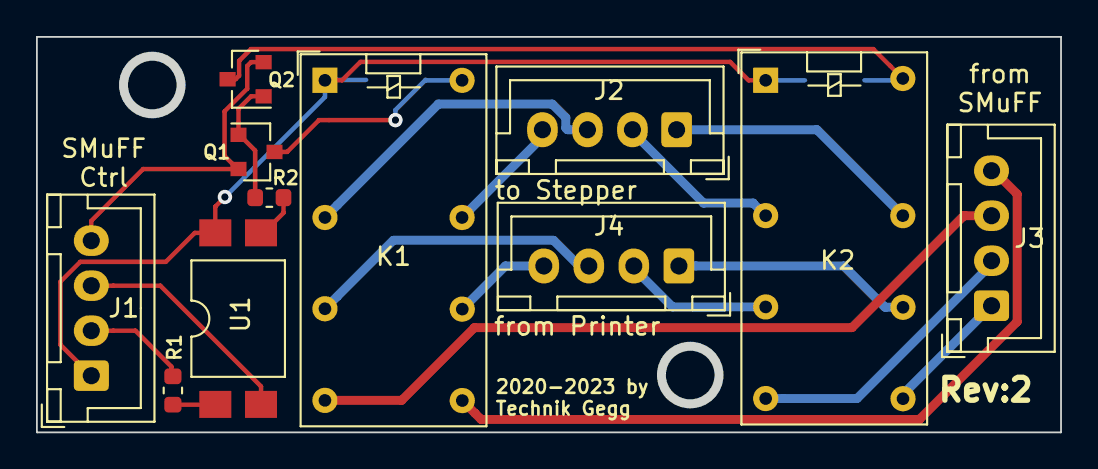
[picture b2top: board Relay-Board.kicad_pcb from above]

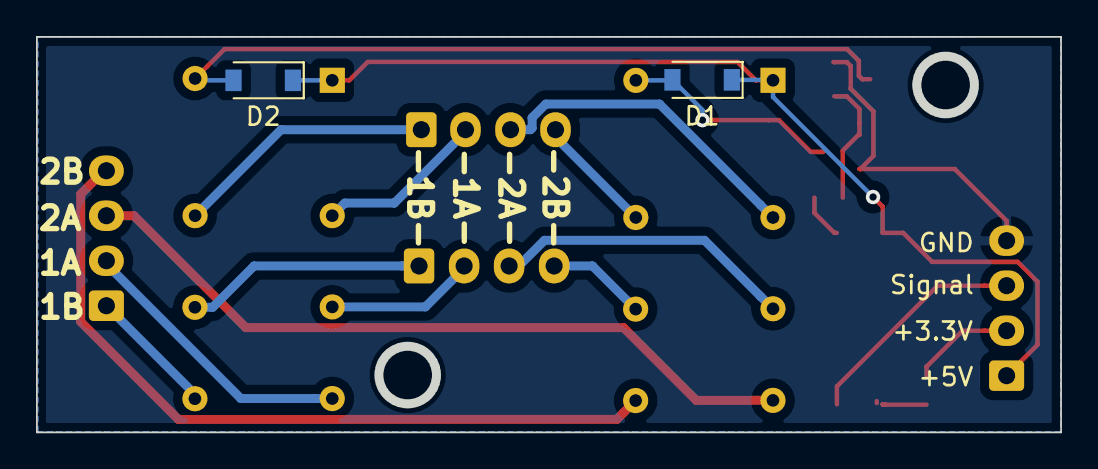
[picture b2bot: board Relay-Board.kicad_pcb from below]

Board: 2 copper layers, 56.9 x 22.0 mm, 13 parts (2 on the bottom side), 21 nets.

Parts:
D1, D2: 1N4148; D_SOD-123
J1, J2, J3, J4: JST XH; JST_XH_B4B-XH-A_1x04_P2.50mm_Vertical
K1, K2: G6A-274P; Relay_DPDT_Omron_G5V-2
Q1, Q2: BC847/547; SOT-23
R1: 390R; R_0603_1608Metric
R2: 1K; R_0603_1608Metric
U1: TLP521; SMDIP-4_W9.53mm_Clearance8mm

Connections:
unnamed: D1.1, D2.1, J1.1, K1.1, K2.1, U1.4
unnamed: D1.2, K1.16, Q1.3
unnamed: D2.2, K2.16, Q2.3
unnamed: J1.2, R1.1
unnamed: J1.3, U1.2
unnamed: J1.4, Q1.2, Q2.2
unnamed: J2.1, K2.13
unnamed: J2.2, K2.4
unnamed: J2.3, K1.4
unnamed: J2.4, K1.13
unnamed: J3.1, K2.9
unnamed: J3.2, K2.8
unnamed: J3.3, K1.8
unnamed: J3.4, K1.9
unnamed: J4.1, K2.11
unnamed: J4.2, K2.6
unnamed: J4.3, K1.6
unnamed: J4.4, K1.11
unnamed: Q1.1, Q2.1, R2.1
unnamed: R1.2, U1.1
unnamed: R2.2, U1.3

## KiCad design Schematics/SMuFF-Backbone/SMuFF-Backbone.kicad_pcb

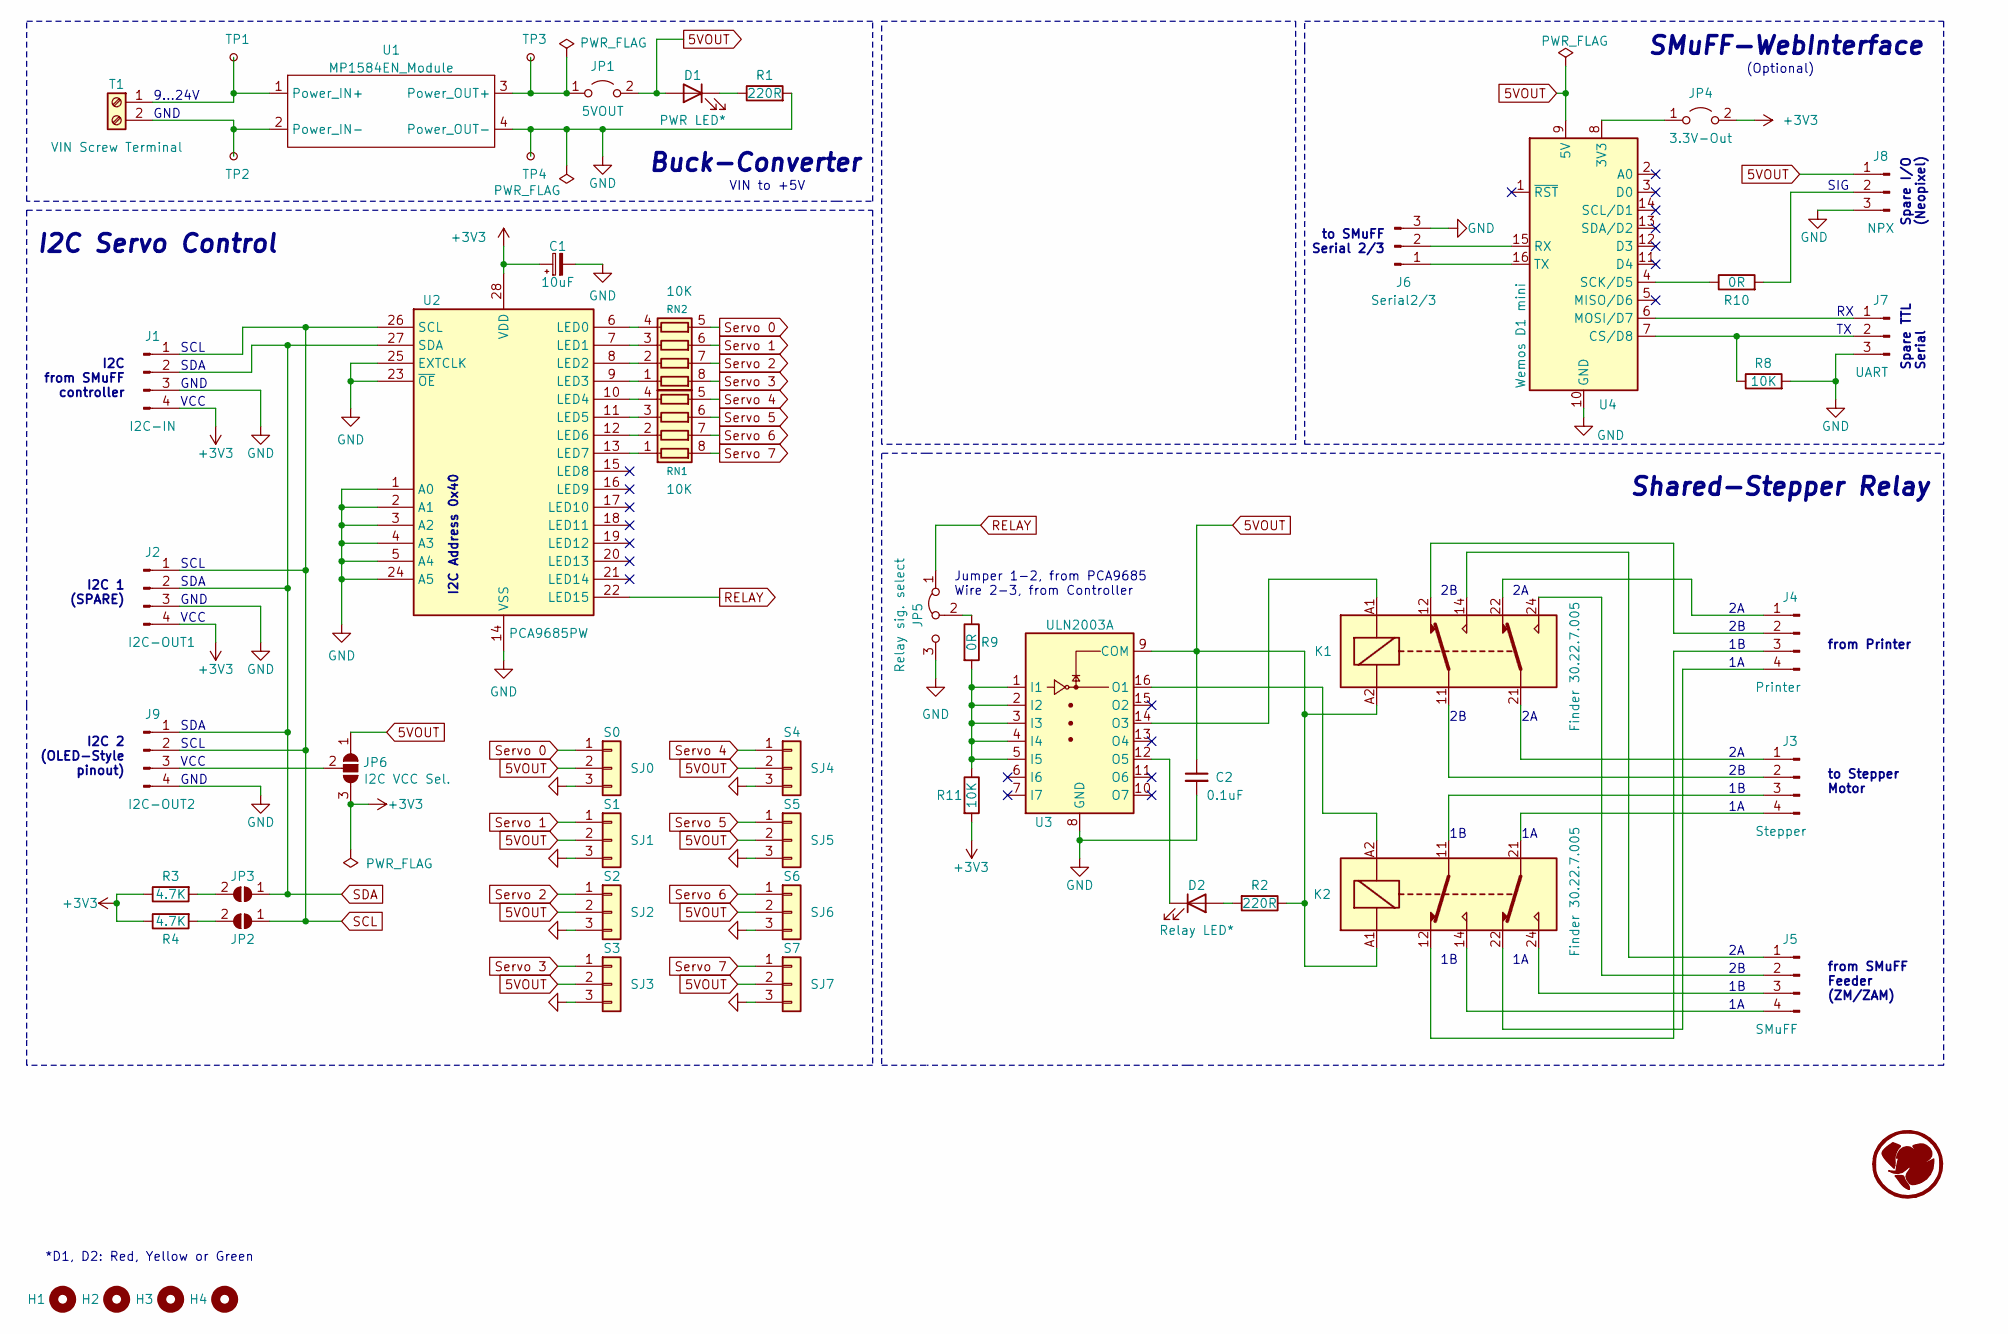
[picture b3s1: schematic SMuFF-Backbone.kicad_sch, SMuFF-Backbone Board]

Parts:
C1: 10uF; C_1206_3216Metric
C2: 0.1uF; C_1206_3216Metric
D1: PWR LED*; LED_1206_3216Metric
D2: Relay LED*; LED_1206_3216Metric
H1, H2, H3, H4: MountingHole; MountingHole_3.2mm_M3
J1: I2C-IN; JST_XH_B4B-XH-A_1x04_P2.50mm_Vertical
J2: I2C-OUT1; PinHeader_1x04_P2.54mm_Vertical
J3: Stepper; JST_XH_B4B-XH-A_1x04_P2.50mm_Vertical
J4: Printer; JST_XH_B4B-XH-A_1x04_P2.50mm_Vertical
J5: SMuFF; JST_XH_B4B-XH-A_1x04_P2.50mm_Vertical
J6: Serial2/3; JST_XH_B3B-XH-A_1x03_P2.50mm_Vertical
J7: UART; JST_XH_B3B-XH-A_1x03_P2.50mm_Vertical
J8: NPX; JST_XH_B3B-XH-A_1x03_P2.50mm_Vertical
J9: I2C-OUT2; PinHeader_1x04_P2.54mm_Vertical
JP1: 5VOUT; PinHeader_1x02_P2.54mm_Vertical
JP2, JP3: Jumper; SolderJumper-2_P1.3mm_Open_RoundedPad1.0x1.5mm
JP4: 3.3V-Out; PinHeader_1x02_P2.54mm_Vertical
JP5: Relay sig. select; PinHeader_1x03_P2.54mm_Vertical
JP6: I2C VCC Sel.; SolderJumper-3_P1.3mm_Open_RoundedPad1.0x1.5mm
K1, K2: Finder 30.22.7.005; Relay_DPDT_Finder_30.22
R1, R2: 220R; R_0805_2012Metric
R3, R4: 4.7K; R_0805_2012Metric
R8, R11: 10K; R_0805_2012Metric
R9, R10: 0R; R_0805_2012Metric
RN1, RN2: 10K; R_Array_Convex_4x0603
SJ0: S0; PinHeader_1x03_P2.54mm_Vertical
SJ1: S1; PinHeader_1x03_P2.54mm_Vertical
SJ2: S2; PinHeader_1x03_P2.54mm_Vertical
SJ3: S3; PinHeader_1x03_P2.54mm_Vertical
SJ4: S4; PinHeader_1x03_P2.54mm_Vertical
SJ5: S5; PinHeader_1x03_P2.54mm_Vertical
SJ6: S6; PinHeader_1x03_P2.54mm_Vertical
SJ7: S7; PinHeader_1x03_P2.54mm_Vertical
T1: VIN Screw Terminal; TerminalBlock_bornier-2_P5.08mm
TP1: SY8205-IN+; TestPoint_THTPad_1.5x1.5mm_Drill0.7mm
TP2: SY8205-IN-; TestPoint_THTPad_1.5x1.5mm_Drill0.7mm
TP3: SY8205-OUT+; TestPoint_THTPad_1.5x1.5mm_Drill0.7mm
TP4: SY8205-OUT-; TestPoint_THTPad_1.5x1.5mm_Drill0.7mm
U1: MP1584EN_Module
U2: PCA9685PW; TSSOP-28_4.4x9.7mm_P0.65mm
U3: ULN2003A; SOIC-16_3.9x9.9mm_P1.27mm
U4: Wemos D1 mini; WEMOS_D1_mini_light

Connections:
5VOUT: C2.1, D1.2 (A), J8.1, JP1.2 (B), JP6.1 (A), K1.A2, K2.A1, R2.1, SJ0.2, SJ1.2, SJ2.2, SJ3.2, SJ4.2, SJ5.2, SJ6.2, SJ7.2, U3.9 (COM), U4.9 (5V)
+3V3: C1.1, J1.4, J2.4, JP4.2 (B), JP6.3 (B), R3.1, R4.1, R11.2, U2.28 (VDD)
GND: C1.2, C2.2, J1.3, J2.3, J6.3, J7.3, J8.3, J9.4, JP5.3 (B), R1.2, R8.2, SJ0.3, SJ1.3, SJ2.3, SJ3.3, SJ4.3, SJ5.3, SJ6.3, SJ7.3, TP4.1, U1.4 (Power_OUT-), U2.1 (A0), U2.2 (A1), U2.3 (A2), U2.4 (A3), U2.5 (A4), U2.14 (VSS), U2.23 (~OE), U2.24 (A5), U2.25 (EXTCLK), U3.8 (GND), U4.10 (GND)
unnamed: D1.1 (K), R1.1
unnamed: D2.2 (A), R2.2
unnamed: D2.1 (K), U3.12 (O5)
unnamed: J3.1, K1.21
unnamed: J3.2, K1.11
unnamed: J3.3, K2.11
unnamed: J3.4, K2.21
unnamed: J4.1, K1.22
unnamed: J4.2, K1.12
unnamed: J4.3, K2.12
unnamed: J4.4, K2.22
unnamed: J5.1, K1.14
unnamed: J5.2, K1.24
unnamed: J5.3, K2.24
unnamed: J5.4, K2.14
unnamed: J6.1, U4.16 (TX)
unnamed: J6.2, U4.15 (RX)
unnamed: J7.1, U4.6 (MOSI/D7)
unnamed: J7.2, R8.1, U4.7 (CS/D8)
unnamed: J8.2, R10.2
unnamed: J9.3, JP6.2 (C)
unnamed: JP1.1 (A), TP3.1, U1.3 (Power_OUT+)
unnamed: JP2.2 (B), R4.2
unnamed: JP3.2 (B), R3.2
unnamed: JP4.1 (A), U4.8 (3V3)
unnamed: JP5.2 (C), R9.1
unnamed: RN1.1 (R1.1), U2.9 (LED3)
unnamed: RN1.2 (R2.1), U2.8 (LED2)
unnamed: RN1.3 (R3.1), U2.7 (LED1)
unnamed: RN1.4 (R4.1), U2.6 (LED0)
unnamed: RN2.1 (R1.1), U2.13 (LED7)
unnamed: RN2.2 (R2.1), U2.12 (LED6)
unnamed: RN2.3 (R3.1), U2.11 (LED5)
unnamed: RN2.4 (R4.1), U2.10 (LED4)
unnamed: T1.1, TP1.1, U1.1 (Power_IN+)
unnamed: T1.2, TP2.1, U1.2 (Power_IN-)
unnamed: R9.2, R11.1, U3.1 (I1), U3.2 (I2), U3.3 (I3), U3.4 (I4), U3.5 (I5)
unnamed: K2.A2, U3.16 (O1)
unnamed: K1.A1, U3.14 (O3)
unnamed: R10.1, U4.4 (SCK/D5)
RELAY: JP5.1 (A), U2.22 (LED15)
SCL: J1.1, J2.1, J9.2, JP2.1 (A), U2.26 (SCL)
SDA: J1.2, J2.2, J9.1, JP3.1 (A), U2.27 (SDA)
Servo 0: RN1.5 (R4.2), SJ0.1
Servo 1: RN1.6 (R3.2), SJ1.1
Servo 2: RN1.7 (R2.2), SJ2.1
Servo 3: RN1.8 (R1.2), SJ3.1
Servo 4: RN2.5 (R4.2), SJ4.1
Servo 5: RN2.6 (R3.2), SJ5.1
Servo 6: RN2.7 (R2.2), SJ6.1
Servo 7: RN2.8 (R1.2), SJ7.1

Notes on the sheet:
SCL
GND
I2C 2 (OLED-Style pinout)
9...24V
I2C from SMuFF controller
Buck-Converter
I2C 1 (SPARE)
Jumper 1-2, from PCA9685 Wire 2-3, from Controller
to Stepper Motor
to SMuFF Serial 2/3
VIN to +5V
I2C Address 0x40
(Optional)
from SMuFF Feeder (ZM/ZAM)
SMuFF-WebInterface
Spare TTL Serial
*D1, D2: Red, Yellow or Green
SDA
SIG
VCC
Spare I/O (Neopixel)
Shared-Stepper Relay
I2C Servo Control
from Printer

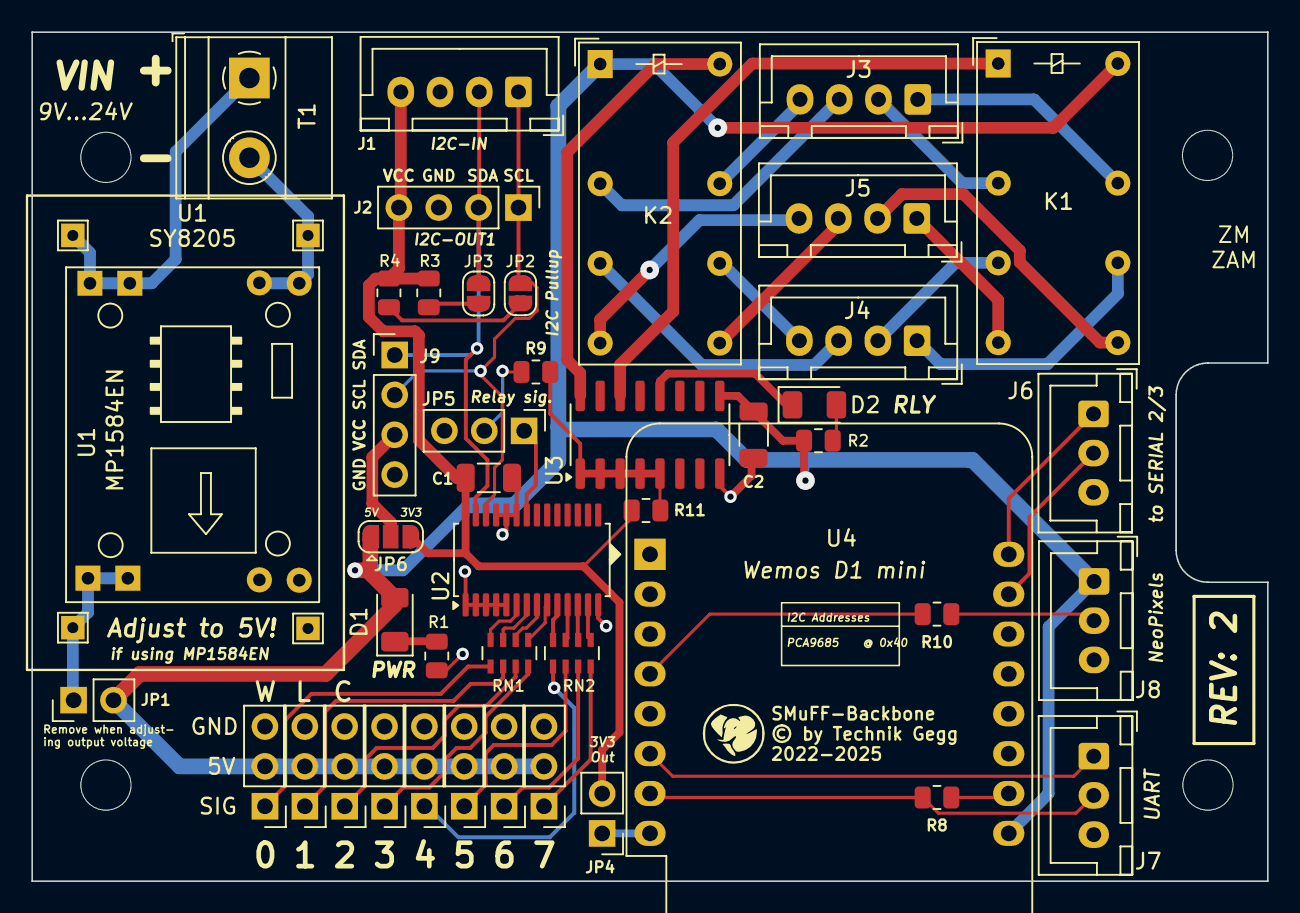
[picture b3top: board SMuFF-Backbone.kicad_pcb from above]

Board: 2 copper layers, 78.7 x 54.1 mm, 52 parts (0 on the bottom side), 54 nets.

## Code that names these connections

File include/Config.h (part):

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#define MAX_ERR_MSG             255                 // max. length of error messages

#define NUM_STEPPERS            3
#define SELECTOR                0
#define REVOLVER                1
#define DDE_FEEDER              1
#define FEEDER                  2
#define FEEDER2                 3                   // added for boards with pre-installed stepper drivers

#define MIN_TOOLS               2
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#define SERVO_CUTTER        2
#define SERVO_SPARE1        3
#define SERVO_SPARE2        4
#define RELAY               5
#define SERVO_USER1         6
#define SERVO_USER2         7
#define D1_MINI_FLASH       13
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#define POWER_SAVE_TIMEOUT      15      // value in seconds

#if !defined(NUM_LEDS)
#define NUM_LEDS                1       // number of Neopixel LEDS
#define BRIGHTNESS              64
#define LED_TYPE                WS2812B
#define COLOR_ORDER             GRB
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
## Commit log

2024-04-12 Changes for I2C scanner; see README.md
2024-04-12 added Wire and SPI to the common lib_debs
2024-04-14 added a few more debug messages
2024-09-18 minor bug fixes (see README.md)
2024-12-02 Updated to 3.30; See README.md

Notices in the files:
include/Config.h:
Copyright (C) 2019-2024 Technik Gegg
This program is free software: you can redistribute it and/or modify
it under the terms of the GNU General Public License as published by
the Free Software Foundation, either version 3 of the License, or
(at your option) any later version.
Schematics/SMuFF-Backbone/SMuFF-Backbone.kicad_pcb:
© by Technik Gegg
